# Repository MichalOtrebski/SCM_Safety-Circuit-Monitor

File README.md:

# SCM - Safety Circuit Monitor
A Circuit that monitors the Safety Circuit on an FS car and toggles LEDs for the most upstream failure point.

## Detailed Description

The purpose of this device is to display to the driver the current state of the Safety system. The safety system is a set of switches and devices which ensure safe operation and shutdown of the car under specific circumstances, once one of these devices is triggered its important for the driver and any technicians to be aware of where exactly the problem is.

## Working Principle

By monitoring various points along the circuit we can determine the most upstream failure point. The Safety Circuit works by driving 12V through various devices in series, the output of the entire stream feeds into automotive relays which then enable power delivery to critial automotive systems such as the ignition coils, fuel pump, and injectors.

So by monitoring the input and output of each device we can determine if 12V is entering the device and if 12V is being output, if a device is not outputing 12V while its input is active then we know that the device has been triggered.

### Signals

The signals we monitor are:

- **BSPD** (Brake System Plausability Device)
- **Inertia** Switch
- **BOTS** (Brake Over Travel Switch)
- **Cockpit** Shutdown Button
- **Left** Shutdown Button
- **Right** Shutdown Button

Hence the Circuit will require six monitoring circut, each looking at the input and output of one device, however since the devices are in series the output of one device is also the input of the next one. 

## Schematic

Each module monitors the input of a device and its output, the basic function is that we use an optocoupler with a pullup, the input of a device acts also as the power source for the module. If we have 12V input into the system we will have a pullup on the output of the optocoupler, which will feed the BJT and sink the external and internal LEDs, showing an error. However if we also have 12V at the output then the pull up sinks to ground via the optocoupler. 

Since the devices are in series, downstream devices wont get any power and no LEDs will be turned on, effectively the system will only light up the most upstream failure point so the driver can focus on reseting it.

## Design Choices

**VOS618A**
- We se an optocoupler to galvanically isolate the input and output between the device, any failure here could bypass the safety device and bring power to the car.
- We use the VOS618A for its high isolation, suitable CTR, and common/cheap availability.

**MMBT2222A**
- We use the BJT here as the driver for the LEDs, sinking their high current.
- we use the MMBT2222A specifically due to its high sinking capacity (600mA & 300mW).z

## Potential Future Revisions

- Increase of possible devices for future safety systems with more than six devices.
- Decrease power consumption (mainly from constantly sinking current through the optocoupler during normal operation)
- adjustable resistor values for varying external LEDs??

## Changelog

**V1.0**
- Initial Design
- Complete Schematic
- Routed PCB
- Verified Behaviour

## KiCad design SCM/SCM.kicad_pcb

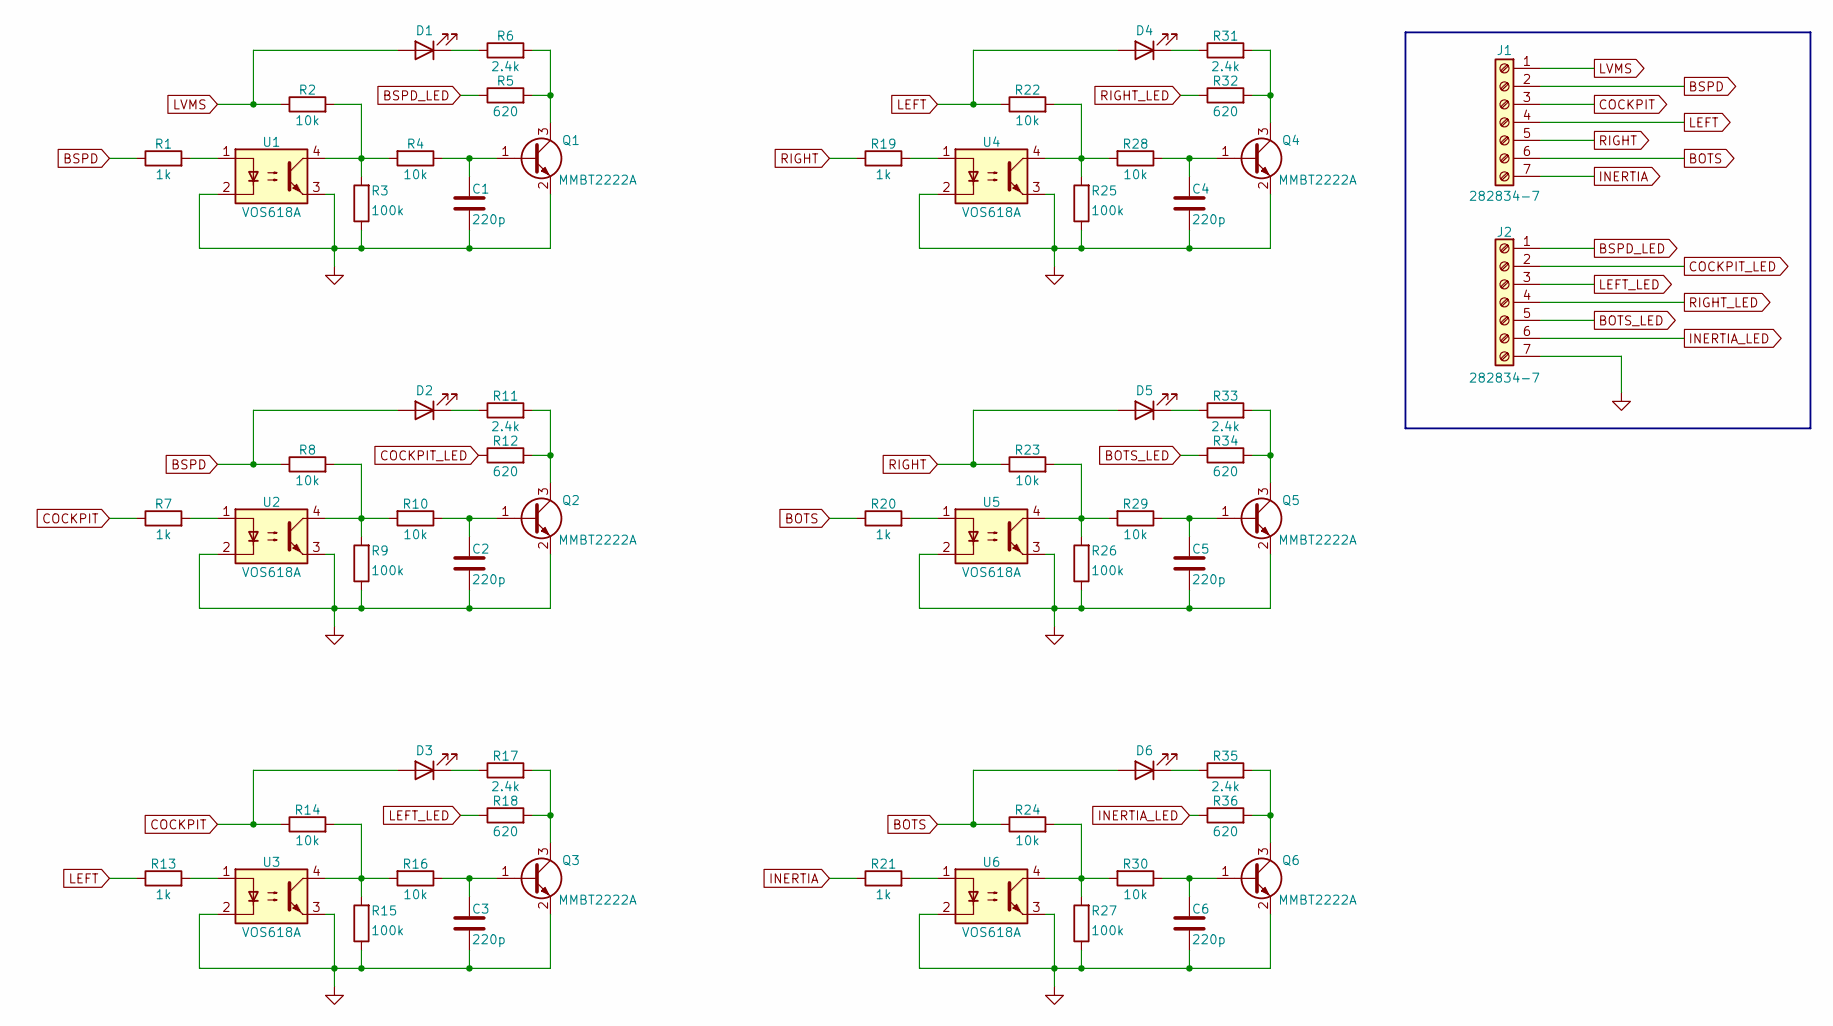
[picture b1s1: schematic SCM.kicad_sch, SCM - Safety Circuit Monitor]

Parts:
C1, C2, C3, C4, C5, C6: 220p; C_0805_2012Metric
D1, D2, D3, D4, D5, D6: LED; LED_0603_1608Metric
J1, J2: 282834-7; TerminalBlock_TE_282834-7_1x07_P2.54mm_Horizontal
Q1, Q2, Q3, Q4, Q5, Q6: MMBT2222A; SOT-23
R1, R7, R13, R19, R20, R21: 1k; R_0805_2012Metric
R2, R4, R8, R10, R14, R16, R22, R23, R24, R28, R29, R30: 10k; R_0805_2012Metric
R3, R9, R15, R25, R26, R27: 100k; R_0805_2012Metric
R5, R12, R18, R32, R34, R36: 620; R_Axial_DIN0207_L6.3mm_D2.5mm_P7.62mm_Horizontal
R6, R11, R17, R31, R33, R35: 2.4k; R_0805_2012Metric
U1, U2, U3, U4, U5, U6: VOS618A; SSOP-4_4.4x2.6mm_P1.27mm

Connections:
BOTS: D6.2 (A), J1.6, R20.1, R24.1
BOTS_LED: J2.5, R34.1
BSPD: D2.2 (A), J1.2, R1.1, R8.1
BSPD_LED: J2.1, R5.1
COCKPIT: D3.2 (A), J1.3, R7.1, R14.1
COCKPIT_LED: J2.2, R12.1
GND: C1.2, C2.2, C3.2, C4.2, C5.2, C6.2, J2.7, Q1.2 (E), Q2.2 (E), Q3.2 (E), Q4.2 (E), Q5.2 (E), Q6.2 (E), R3.1, R9.1, R15.1, R25.1, R26.1, R27.1, U1.2, U1.3, U2.2, U2.3, U3.2, U3.3, U4.2, U4.3, U5.2, U5.3, U6.2, U6.3
INERTIA: J1.7, R21.1
INERTIA_LED: J2.6, R36.1
LEFT: D4.2 (A), J1.4, R13.1, R22.1
LEFT_LED: J2.3, R18.1
LVMS: D1.2 (A), J1.1, R2.1
unnamed: D1.1 (K), R6.1
unnamed: D2.1 (K), R11.1
unnamed: D3.1 (K), R17.1
unnamed: D4.1 (K), R31.1
unnamed: D5.1 (K), R33.1
unnamed: D6.1 (K), R35.1
unnamed: C1.1, Q1.1 (B), R4.1
unnamed: Q1.3 (C), R5.2, R6.2
unnamed: C2.1, Q2.1 (B), R10.1
unnamed: Q2.3 (C), R11.2, R12.2
unnamed: C3.1, Q3.1 (B), R16.1
unnamed: Q3.3 (C), R17.2, R18.2
unnamed: C4.1, Q4.1 (B), R28.1
unnamed: Q4.3 (C), R31.2, R32.2
unnamed: C5.1, Q5.1 (B), R29.1
unnamed: Q5.3 (C), R33.2, R34.2
unnamed: C6.1, Q6.1 (B), R30.1
unnamed: Q6.3 (C), R35.2, R36.2
unnamed: R1.2, U1.1
unnamed: R2.2, R3.2, R4.2, U1.4
unnamed: R7.2, U2.1
unnamed: R8.2, R9.2, R10.2, U2.4
unnamed: R13.2, U3.1
unnamed: R14.2, R15.2, R16.2, U3.4
unnamed: R19.2, U4.1
unnamed: R20.2, U5.1
unnamed: R21.2, U6.1
unnamed: R22.2, R25.2, R28.2, U4.4
unnamed: R23.2, R26.2, R29.2, U5.4
unnamed: R24.2, R27.2, R30.2, U6.4
RIGHT: D5.2 (A), J1.5, R19.1, R23.1
RIGHT_LED: J2.4, R32.1

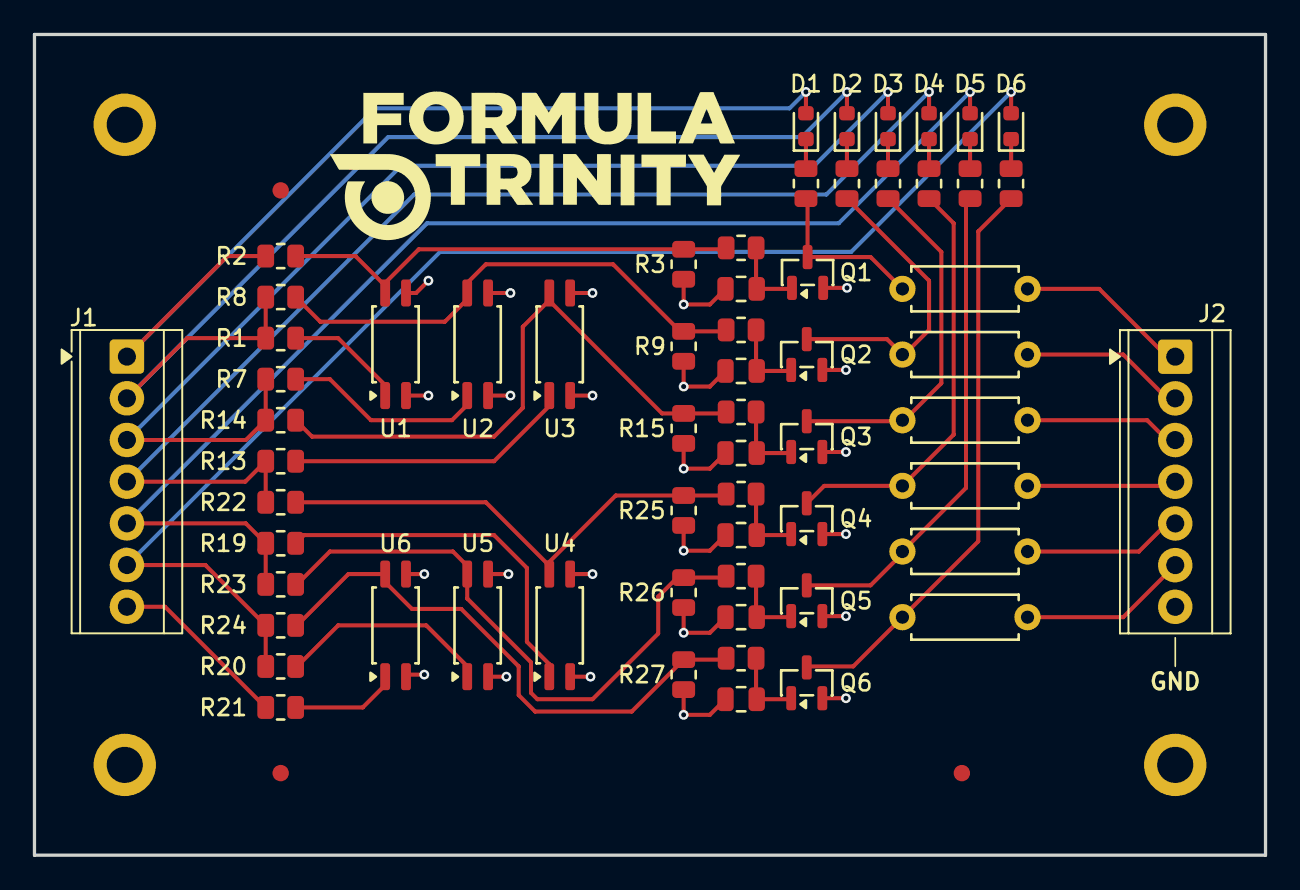
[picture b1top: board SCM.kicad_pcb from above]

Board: 2 copper layers, 75.0 x 50.0 mm, 62 parts (0 on the bottom side), 44 nets.

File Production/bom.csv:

Designator,Footprint,Quantity,Value,LCSC Part #
"C1, C2, C3, C4, C5, C6",0805,6,220p,
"D1, D2, D3, D4, D5, D6",0603,6,LED,
"J1, J2",TerminalBlock_TE_282834-7_1x07_P2.54mm_Horizontal,2,Screw_Terminal_01x07,
"Q1, Q2, Q3, Q4, Q5, Q6",SOT-23,6,MMBT2222A,
"R1, R13, R19, R20, R21, R7",0805,6,1k,
"R10, R14, R16, R2, R22, R23, R24, R28, R29, R30, R4, R8",0805,12,10k,
"R11, R17, R31, R33, R35, R6",0805,6,2.4k,
"R12, R18, R32, R34, R36, R5",R_Axial_DIN0207_L6.3mm_D2.5mm_P7.62mm_Horizontal,6,620,
"R15, R25, R26, R27, R3, R9",0805,6,100k,
"U1, U2, U3, U4, U5, U6",SSOP-4_4.4x2.6mm_P1.27mm,6,VOS618A,

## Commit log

2026-03-26 Full SCM commit and Readme
